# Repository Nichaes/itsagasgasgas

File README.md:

# Its a gas gas gas

Arduino shield for biogas systems. Sensing temperature & methan

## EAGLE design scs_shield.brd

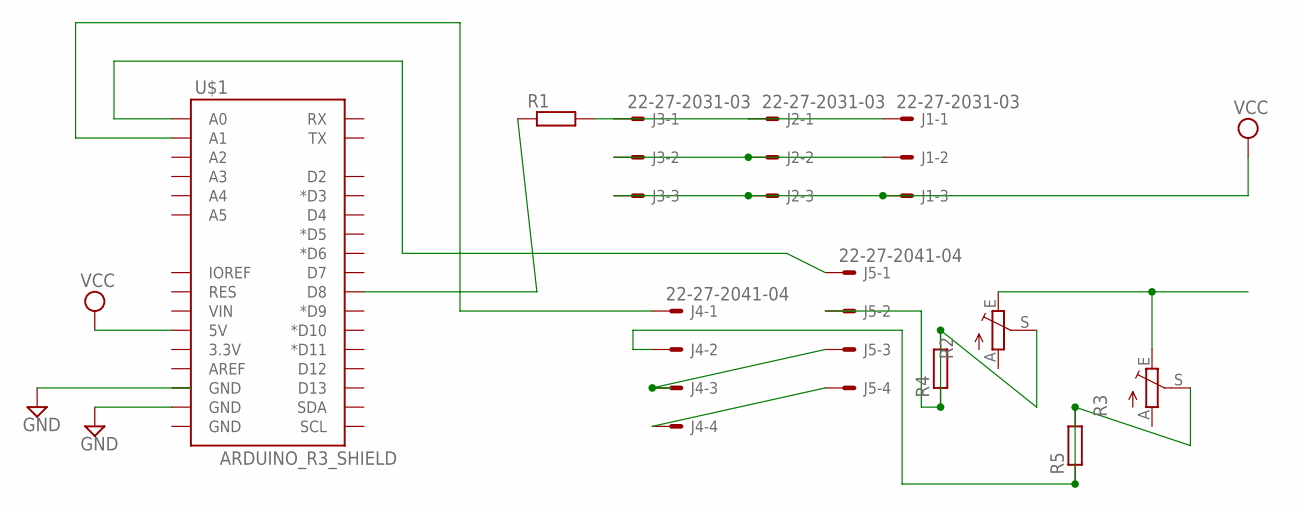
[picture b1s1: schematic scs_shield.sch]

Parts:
J1, J2, J3: 22-27-2031-03; 6410-03
J4, J5: 22-27-2041-04; 6410-04
R1, R4, R5: R-EU_0204/5; 0204/5
R2, R3: TRIM_EU-CA6V; CA6V
U$1: ARDUINO_R3_SHIELD; UNO_R3_SHIELD

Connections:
unnamed: J1.1, J2.1, J3.1, R1.2
unnamed: J4.2, R3.S, R5.1, R5.2
unnamed: R1.1, U$1.D8
unnamed: J5.2, R2.S, R4.1, R4.2
unnamed: J5.1, U$1.A0
unnamed: J4.1, U$1.A1
unnamed: J4.3, J5.3, R2.E, R3.E, U$1.GND@1 (GND)
unnamed: J1.2, J2.2, J3.2
unnamed: J4.4, J5.4
VCC: J1.3, J2.3, J3.3, U$1.5V

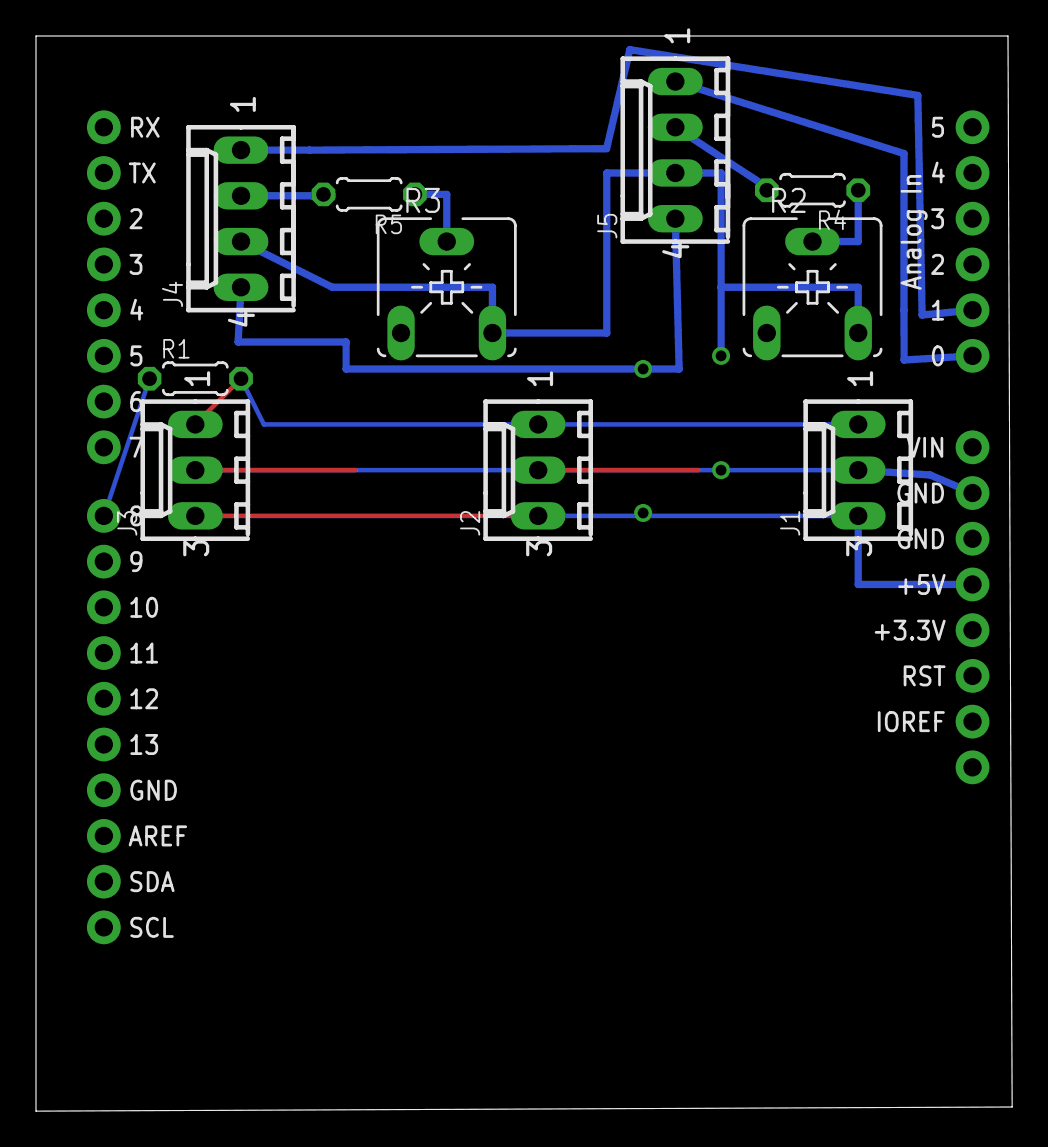
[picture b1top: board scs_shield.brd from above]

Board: 2 copper layers, 54.2 x 59.7 mm, 11 parts (0 on the bottom side), 10 nets.

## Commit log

2014-08-20 Readme.md

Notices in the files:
parts and their libraries:
SparkFun-Boards: Licensing: Creative Commons ShareAlike 4.0 International - https://creativecommons.org/licenses/by-sa/4.0
